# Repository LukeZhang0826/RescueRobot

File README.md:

# RescueRobot

An autonomous line-following rescue robot, built for a competition at the University of
Waterloo's IDEAS Clinic. It follows a track, finds a coloured target, picks it up with a
servo claw, carries it to a safe zone, drops it, then finds the line again and drives
back.

We called it Hamster, which is why the robot code lives in `Hamster/`.

**[Watch the run](https://youtu.be/ffi4BYylVoE)** ·
**[Final report](https://docs.google.com/document/d/1Vht0kWhE6cIuxJ4qUaxeXvZQmihU7ujaP2H0h0Pqgro/edit)**

Built by Josh Lobe, Koketso Gaborekwe, Luke Zhang, Winters Xia, and Griffin Wilson.

## The mission

`Hamster/robot_mission.py` is a flat state machine. A button press starts it, and every
stage either advances or drops into an error state.

```
idle -> search_line_follow -> approach_target -> pickup -> holding_object
     -> turn_around -> rescue_line_follow -> approach_safe_zone -> release
     -> find_line -> return_line_follow -> done
```

Three separate line followers exist because each leg of the run has different exit
conditions. `search_line_follower` stops when the target is large enough in frame,
`rescue_line_follower` stops on the safe zone signature, and `return_line_follow` runs
the trip home. All three share a PD steering loop over the Pixy2 line centroid, with a
recovery state that turns back toward the side the line was last seen on.

## Hardware

| Part | Notes |
| --- | --- |
| Raspberry Pi Pico | Runs the MicroPython mission code in `Hamster/` |
| Arduino Mega 2560 | PlatformIO firmware in `firmware/`, used for board bring-up |
| Pixy2 camera | Line tracking and colour connected component detection, 7 signatures |
| DRV8833 | Dual motor driver, signed speed from -100 to +100 |
| Servo claw | Pickup and release |
| Custom PCBs | An Arduino Mega shield and a base board, KiCad sources in `Electrical/` |

Both PCBs were manufactured through JLCPCB. Gerbers, BOM, and pick-and-place files are
committed under `Electrical/KiCad/BasePCB/jlcpcb/`.

## Layout

| Path | What it is |
| --- | --- |
| `Hamster/` | MicroPython mission code for the Pico |
| `Hamster/archive/` | Superseded scripts kept from earlier milestones |
| `Hamster/pixycamParams/` | Saved Pixy2 tuning, including the values used on the day |
| `firmware/` | PlatformIO project for the Arduino Mega |
| `Electrical/KiCad/` | KiCad projects, gerbers, and production files |

## Running it

The Pico code is deployed with the MicroPico VS Code extension. Copy the contents of
`Hamster/` to the board and reset it. `Hamster/main.py` wires up the hardware objects and
hands control to `RobotMission.run_once()`, which waits for the start button.

Everything the robot is tuned by lives in `Hamster/config.py`, including the PI gains per
wheel, the PD steering constants, base speeds in RPM, and the Pixy2 area thresholds that
decide when a target is close enough to stop. The competition values are the ones
currently committed.

For the Arduino side, `cd firmware && pio run -t upload`.

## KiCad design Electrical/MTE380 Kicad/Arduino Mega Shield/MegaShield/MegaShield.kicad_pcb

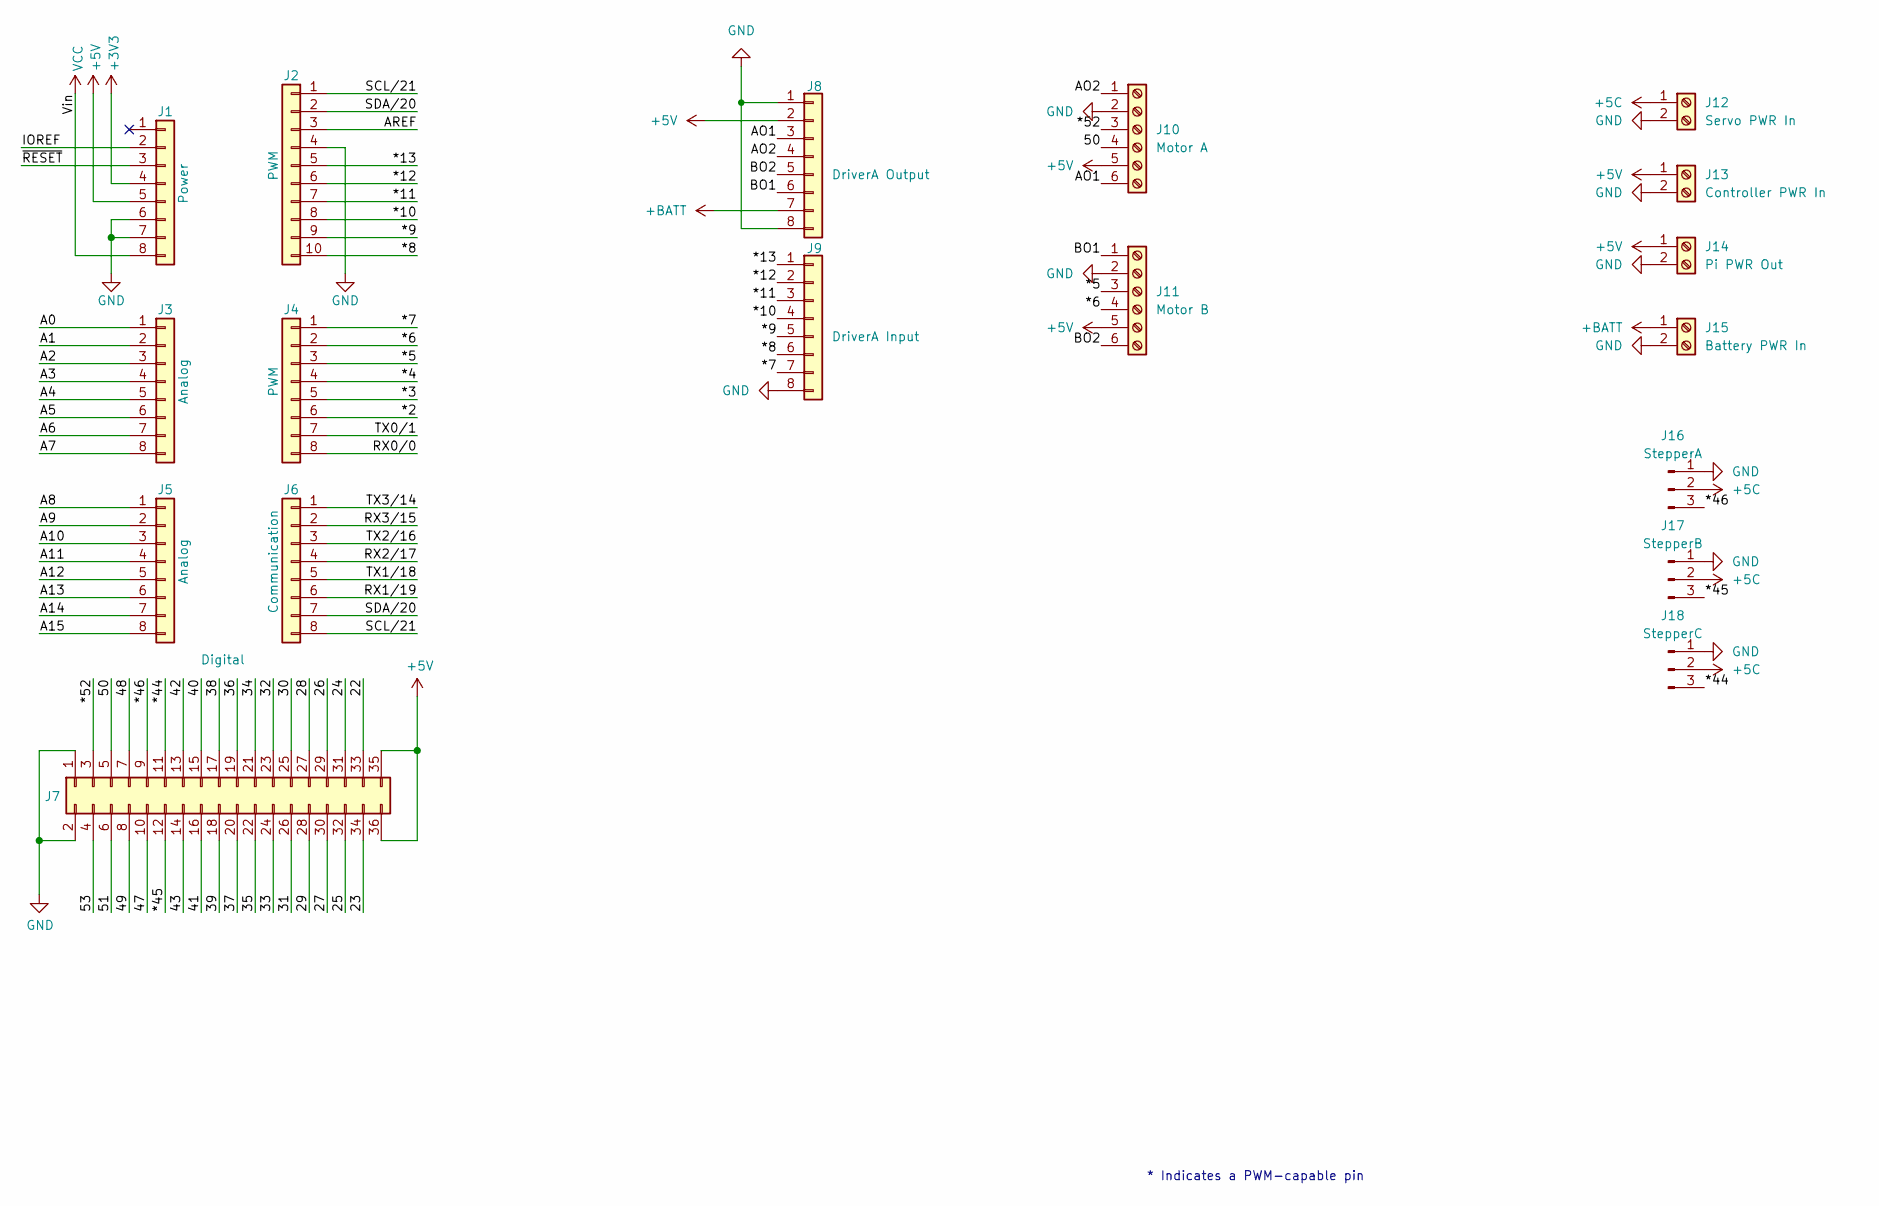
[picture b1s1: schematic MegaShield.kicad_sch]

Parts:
J1: Power; PinSocket_1x08_P2.54mm_Vertical
J2: PWM; PinSocket_1x10_P2.54mm_Vertical
J3, J5: Analog; PinSocket_1x08_P2.54mm_Vertical
J4: PWM; PinSocket_1x08_P2.54mm_Vertical
J6: Communication; PinSocket_1x08_P2.54mm_Vertical
J7: Digital; PinSocket_2x18_P2.54mm_Vertical
J8: DriverA Output; PinSocket_1x08_P2.54mm_Vertical
J9: DriverA Input; PinSocket_1x08_P2.54mm_Vertical
J10: Motor A; TerminalBlock_4Ucon_1x06_P3.50mm_Horizontal
J11: Motor B; TerminalBlock_4Ucon_1x06_P3.50mm_Horizontal
J12: Servo PWR In; TerminalBlock_CUI_TB007-508-02_1x02_P5.08mm_Horizontal
J13: Controller PWR In; TerminalBlock_CUI_TB007-508-02_1x02_P5.08mm_Horizontal
J14: Pi PWR Out; TerminalBlock_CUI_TB007-508-02_1x02_P5.08mm_Horizontal
J15: Battery PWR In; TerminalBlock_CUI_TB007-508-02_1x02_P5.08mm_Horizontal
J16: StepperA; PinSocket_1x03_P2.54mm_Vertical
J17: StepperB; PinSocket_1x03_P2.54mm_Vertical
J18: StepperC; PinSocket_1x03_P2.54mm_Vertical

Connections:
+3V3: J1.4
+5C: J12.1, J16.2, J17.2, J18.2
+5V: J1.5, J7.35, J7.36, J8.2, J10.5, J11.5, J13.1, J14.1
+BATT: J8.7, J15.1
/22: J7.33
/23: J7.34
/24: J7.31
/25: J7.32
/26: J7.29
/27: J7.30
/28: J7.27
/29: J7.28
/30: J7.25
/31: J7.26
/32: J7.23
/33: J7.24
/34: J7.21
/35: J7.22
/36: J7.19
/37: J7.20
/38: J7.17
/39: J7.18
/40: J7.15
/41: J7.16
/42: J7.13
/43: J7.14
/47: J7.10
/48: J7.7
/49: J7.8
/50: J7.5, J10.4
/51: J7.6
/53: J7.4
/*2: J4.6
/*3: J4.5
/*4: J4.4
/*5: J4.3, J11.3
/*6: J4.2, J11.4
/*7: J4.1, J9.7
/*8: J2.10, J9.6
/*9: J2.9, J9.5
/*10: J2.8, J9.4
/*11: J2.7, J9.3
/*12: J2.6, J9.2
/*13: J2.5, J9.1
/*44: J7.11, J18.3
/*45: J7.12, J17.3
/*46: J7.9, J16.3
/*52: J7.3, J10.3
/A0: J3.1
/A1: J3.2
/A2: J3.3
/A3: J3.4
/A4: J3.5
/A5: J3.6
/A6: J3.7
/A7: J3.8
/A8: J5.1
/A9: J5.2
/A10: J5.3
/A11: J5.4
/A12: J5.5
/A13: J5.6
/A14: J5.7
/A15: J5.8
/AO1: J8.3, J10.6
/AO2: J8.4, J10.1
/AREF: J2.3
/BO1: J8.6, J11.1
/BO2: J8.5, J11.6
/IOREF: J1.2
/RX0/0: J4.8
/RX1/19: J6.6
/RX2/17: J6.4
/RX3/15: J6.2
/SCL/21: J2.1, J6.8
/SDA/20: J2.2, J6.7
/TX0/1: J4.7
/TX1/18: J6.5
/TX2/16: J6.3
/TX3/14: J6.1
/~RESET: J1.3
GND: J1.6, J1.7, J2.4, J7.1, J7.2, J8.1, J8.8, J9.8, J10.2, J11.2, J12.2, J13.2, J14.2, J15.2, J16.1, J17.1, J18.1
VCC: J1.8

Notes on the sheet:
* Indicates a PWM-capable pin

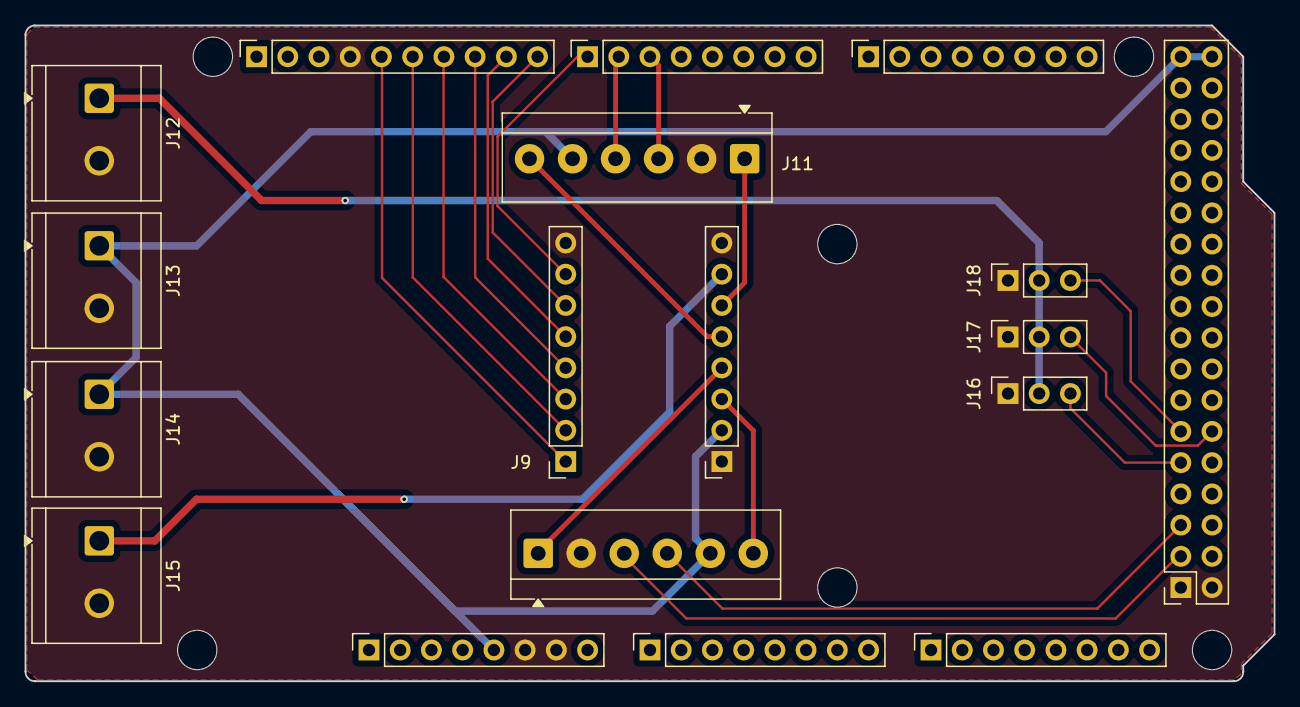
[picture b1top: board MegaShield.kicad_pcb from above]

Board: 2 copper layers, 101.6 x 53.3 mm, 24 parts (0 on the bottom side), 24 nets.

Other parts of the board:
MH1, MH2, MH3, MH4, MH5, MH6: MountingHole_3.2mm

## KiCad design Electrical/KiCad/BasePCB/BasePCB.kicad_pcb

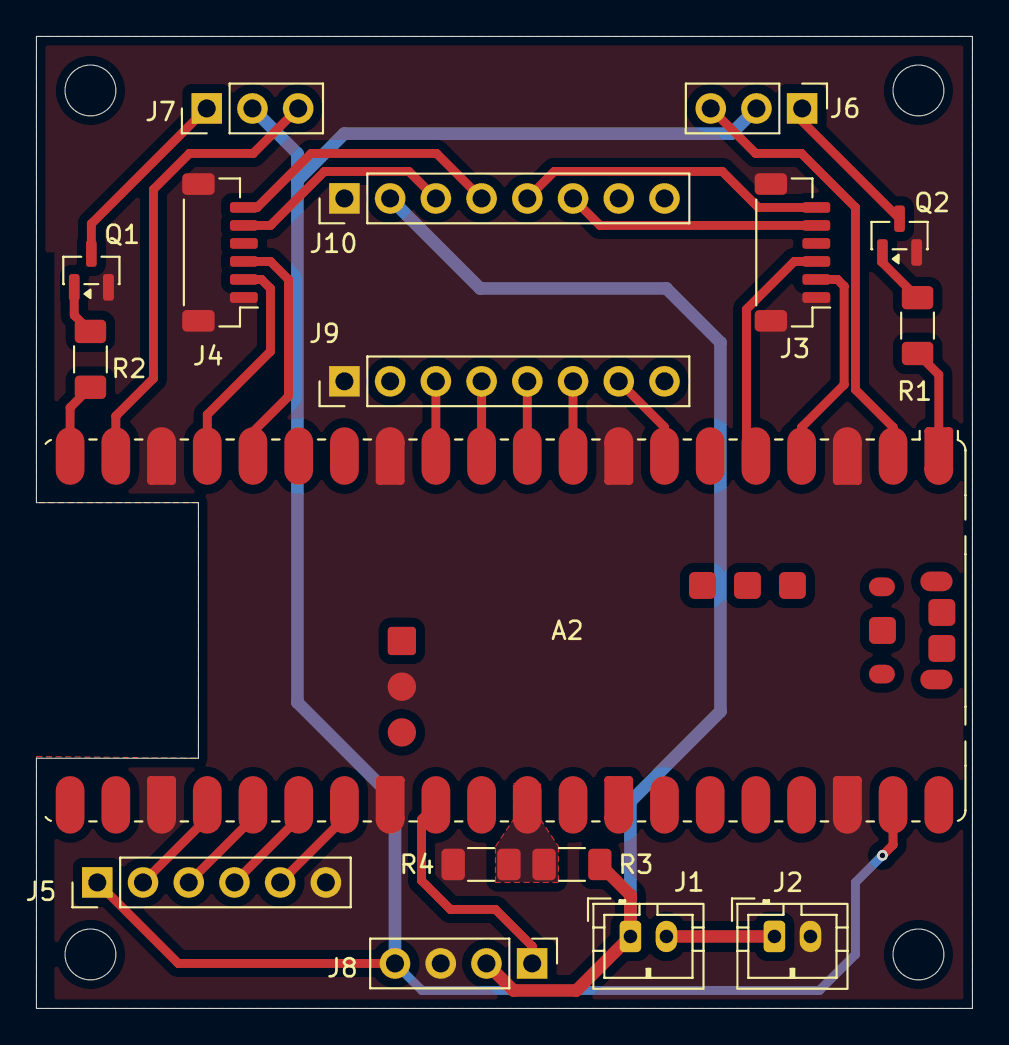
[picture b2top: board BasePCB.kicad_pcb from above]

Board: 2 copper layers, 52.0 x 54.0 mm, 17 parts (0 on the bottom side), 32 nets.

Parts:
A2: RaspberryPi_Pico_W; RaspberryPi_Pico_W_SMD
J1, J2: Conn_01x02_Socket; JST_PH_B2B-PH-K_1x02_P2.00mm_Vertical
J3, J4: Conn_01x06_Socket; JST_SH_BM06B-SRSS-TB_1x06-1MP_P1.00mm_Vertical
J5: Conn_01x06; PinHeader_1x06_P2.54mm_Vertical
J6, J7: Conn_01x03; PinHeader_1x03_P2.54mm_Vertical
J8: Conn_01x04; PinHeader_1x04_P2.54mm_Vertical
J9, J10: Conn_01x08; PinHeader_1x08_P2.54mm_Vertical
Q1, Q2: AO3400A; SOT-23
R1, R2: 10k; R_1206_3216Metric_Pad1.30x1.75mm_HandSolder
R3: 100k; R_1206_3216Metric_Pad1.30x1.75mm_HandSolder
R4: 56k; R_1206_3216Metric_Pad1.30x1.75mm_HandSolder

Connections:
+3.3V: A2.36 (3V3), J3.4, J4.4
+5V: A2.39 (VSYS), J5.1, J6.2, J7.2, J8.4
+BATT: J1.1, J8.2, J10.2, R3.1
/5V_EN: A2.29 (GPIO22), J8.1
/AIN1: A2.9 (GPIO6), J9.6
/AIN2: A2.10 (GPIO7), J9.5
/BIN1: A2.12 (GPIO9), J9.3
/BIN2: A2.11 (GPIO8), J9.4
/CLK: A2.24 (GPIO18), J5.2
/CS: A2.27 (GPIO21), J5.5
/EA1: A2.4 (GPIO2), J3.2
/EA2: A2.5 (GPIO3), J3.3
/EB1: A2.17 (GPIO13), J4.2
/EB2: A2.16 (GPIO12), J4.3
/MA1: J3.5, J10.6
/MA2: J3.6, J10.5
/MB1: J4.5, J10.3
/MB2: J4.6, J10.4
/MISO: A2.26 (GPIO20), J5.4
/MOSI: A2.25 (GPIO19), J5.3
/SA_PWM: A2.2 (GPIO1), J6.3
/SA_PWR: A2.1 (GPIO0), R1.1
/SB_PWM: A2.19 (GPIO14), J7.3
/SB_PWR: A2.20 (GPIO15), R2.1
/Vchg: A2.31 (GPIO26_ADC0), R3.2, R4.1
/nSLEEP: A2.7 (GPIO5), J9.7
GND: A2.3 (GND), A2.8 (GND), A2.13 (GND), A2.18 (GND), A2.23 (GND), A2.28 (GND), A2.38 (GND), A2.D2 (GND), J2.2, J3.1, J3.MP, J4.1, J4.MP, J5.6, J8.3, J9.1, J10.1, Q1.2 (S), Q2.2 (S), R4.2
unnamed: J1.2, J2.1
unnamed: J6.1, Q2.3 (D)
unnamed: J7.1, Q1.3 (D)
unnamed: Q1.1 (G), R2.2
unnamed: Q2.1 (G), R1.2

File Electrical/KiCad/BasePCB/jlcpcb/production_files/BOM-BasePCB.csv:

Comment,Designator,Footprint,LCSC,Quantity
Conn_01x06_Socket,J3,JST_SH_BM06B-SRSS-TB_1x06-1MP_P1.00mm_Vertical,,1
RaspberryPi_Pico_W,A2,RaspberryPi_Pico_W_SMD,,1
10k,R2,R_1206_3216Metric_Pad1.30x1.75mm_HandSolder,,1
Conn_01x06_Socket,J4,JST_SH_BM06B-SRSS-TB_1x06-1MP_P1.00mm_Vertical,,1
10k,R1,R_1206_3216Metric_Pad1.30x1.75mm_HandSolder,,1
AO3400A,Q2,SOT-23,,1
Conn_01x03,J7,PinHeader_1x03_P2.54mm_Vertical,,1
Conn_01x03,J6,PinHeader_1x03_P2.54mm_Vertical,,1
Conn_01x02_Socket,J1,JST_PH_B2B-PH-K_1x02_P2.00mm_Vertical,,1
Conn_01x02_Socket,J2,JST_PH_B2B-PH-K_1x02_P2.00mm_Vertical,,1
Conn_01x08,J10,PinHeader_1x08_P2.54mm_Vertical,,1
Conn_01x08,J9,PinHeader_1x08_P2.54mm_Vertical,,1
56k,R4,R_1206_3216Metric_Pad1.30x1.75mm_HandSolder,,1
100k,R3,R_1206_3216Metric_Pad1.30x1.75mm_HandSolder,,1
Conn_01x04,J8,PinHeader_1x04_P2.54mm_Vertical,,1
AO3400A,Q1,SOT-23,,1
Conn_01x06,J5,PinHeader_1x06_P2.54mm_Vertical,,1

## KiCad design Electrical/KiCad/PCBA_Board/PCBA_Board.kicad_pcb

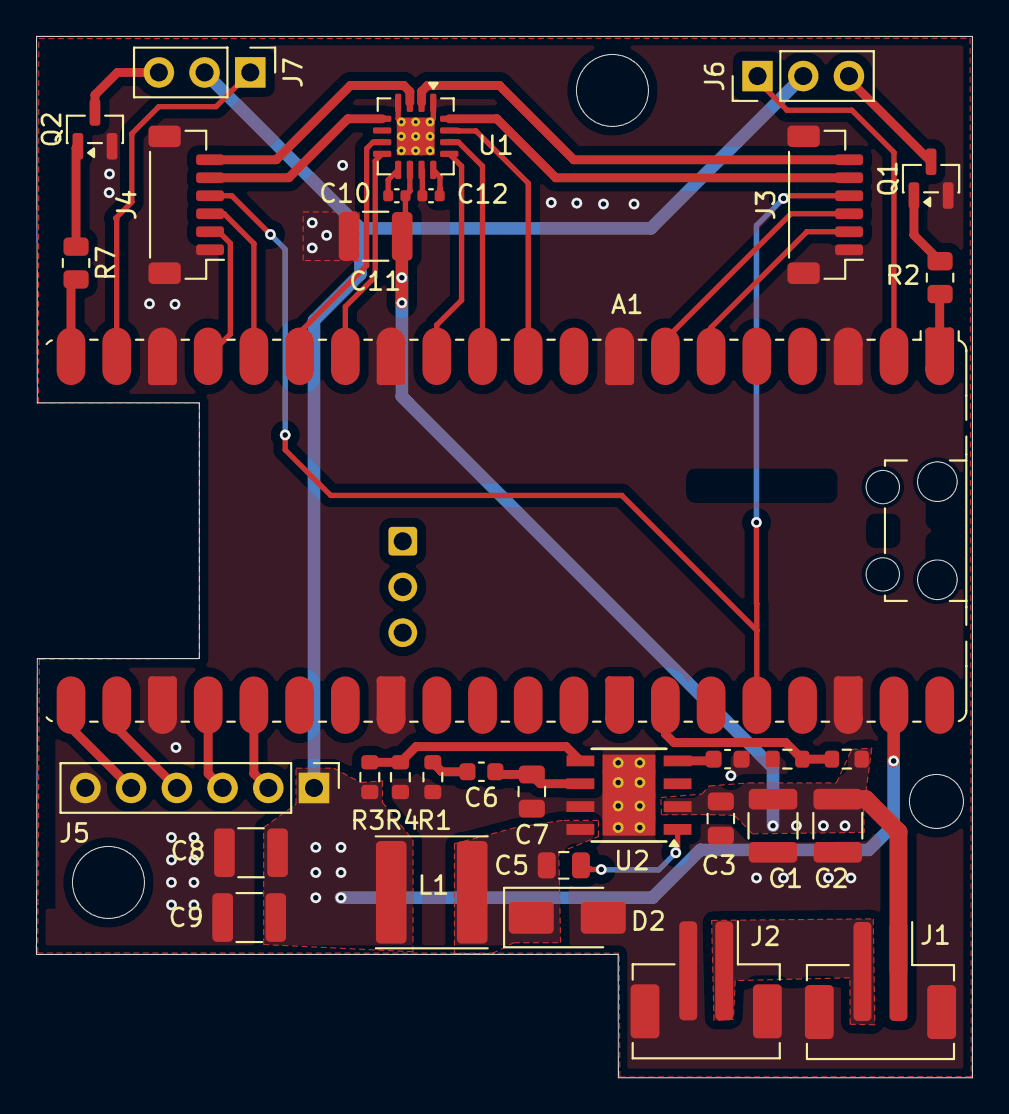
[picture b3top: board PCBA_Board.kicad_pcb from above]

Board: 2 copper layers, 52.0 x 57.8 mm, 33 parts (0 on the bottom side), 39 nets.

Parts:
A1: RaspberryPi_Pico_W; RaspberryPi_Pico_W_SMD_HandSolder
C1, C2: 4.7uF; C_1210_3225Metric
C3: 0.01uF; C_0805_2012Metric
C4: 8.2nF; C_0603_1608Metric
C5: 100nF; C_0805_2012Metric
C6: 1nF; C_0603_1608Metric
C7: 10pF; C_0805_2012Metric
C8, C9: 47u; C_1210_3225Metric
C10: 0.01u; C_0402_1005Metric
C11: 10u; C_1210_3225Metric
C12: 2.2u; C_0402_1005Metric
D2: SS24; D_SMA
J1: Batt_1; JST_PH_B2B-PH-SM4-TB_1x02-1MP_P2.00mm_Vertical
J2: Batt_2; JST_PH_B2B-PH-SM4-TB_1x02-1MP_P2.00mm_Vertical
J3: MotorA; JST_SH_BM06B-SRSS-TB_1x06-1MP_P1.00mm_Vertical
J4: MotorB; JST_SH_BM06B-SRSS-TB_1x06-1MP_P1.00mm_Vertical
J5: Pixy SPI Connection; PinHeader_1x06_P2.54mm_Vertical
J6: ServoA; PinHeader_1x03_P2.54mm_Vertical
J7: ServoB; PinHeader_1x03_P2.54mm_Vertical
L1: 4.7u; L_APV_ANR6028
Q1, Q2: AO3400A; SOT-23
R1: 66.5k; R_0603_1608Metric
R2, R7: 100k; R_0805_2012Metric
R3: 10.2k; R_0603_1608Metric
R4: 1.96k; R_0603_1608Metric
R5: 570K; R_0603_1608Metric
R6: 330K; R_0603_1608Metric
U1: DRV8833RTY; Texas_RTY_WQFN-16-1EP_4x4mm_P0.65mm_EP2.1x2.1mm_ThermalVias
U2: TPS54331; TI_SO-PowerPAD-8_ThermalVias

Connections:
+3.3V: A1.36 (3V3), J3.4, J4.4
+5V: A1.39 (VSYS), C8.1, C9.1, J5.1, J6.2, J7.2, L1.2, R3.1
+BATT: C1.1, C2.1, C3.1, C10.1, C11.1, J1.1, R5.1, U1.10 (VM), U2.2 (Vin)
/AIN1: A1.11 (GPIO8), U1.14 (AIN1)
/AIN2: A1.12 (GPIO9), U1.13 (AIN2)
/AOUT1: J3.5, U1.16 (AOUT1)
/AOUT2: J3.6, U1.2 (AOUT2)
/BIN1: A1.15 (GPIO11), U1.7 (BIN1)
/BIN2: A1.14 (GPIO10), U1.8 (BIN2)
/BOUT1: J4.5, U1.5 (BOUT1)
/BOUT2: J4.6, U1.3 (BOUT2)
/CS: A1.22 (GPIO17), J5.4
/ENC_A1: A1.6 (GPIO4), J3.2
/ENC_A2: A1.7 (GPIO5), J3.3
/ENC_B1: A1.17 (GPIO13), J4.2
/ENC_B2: A1.16 (GPIO12), J4.3
/MISO: A1.21 (GPIO16), J5.5
/MOSI: A1.25 (GPIO19), J5.2
/SCK: A1.24 (GPIO18), J5.3
/ServoA_PWM: A1.2 (GPIO1), J6.1
/ServoA_PWR: A1.1 (GPIO0), R2.2
/ServoB_PWM: A1.19 (GPIO14), J7.1
/ServoB_PWR: A1.20 (GPIO15), R7.2
/VbatSense: A1.34 (GPIO28_ADC2), R5.2, R6.1
/Vsns: R3.2, R4.1, U2.5 (Vsense)
/nSleep: A1.10 (GPIO7), U1.15 (~SLEEP)
GND: A1.3 (GND), A1.8 (GND), A1.13 (GND), A1.18 (GND), A1.23 (GND), A1.28 (GND), A1.38 (GND), C1.2, C2.2, C3.2, C4.2, C7.2, C8.2, C9.2, C11.2, C12.1, D2.2 (A), J1.MP (MountPin), J2.2, J2.MP (MountPin), J3.1, J3.MP (MountPin), J4.1, J4.MP (MountPin), J5.6, Q1.2 (S), Q2.2 (S), R1.2, R4.2, R6.2, U1.1 (AISEN), U1.4 (BISEN), U1.11 (GND), U1.17 (GND), U2.7 (GND), U2.9 (EP)
unnamed: C6.2, R1.1
unnamed: C5.1, D2.1 (K), L1.1, U2.8 (PH)
unnamed: J1.2, J2.1
unnamed: J6.3, Q1.3 (D)
unnamed: J7.3, Q2.3 (D)
unnamed: Q1.1 (G), R2.1
unnamed: Q2.1 (G), R7.1
unnamed: C10.2, U1.9 (VCP)
unnamed: C12.2, U1.12 (VINT)
unnamed: C5.2, U2.1 (BOOT)
unnamed: C6.1, C7.1, U2.6 (COMP)
unnamed: C4.1, U2.4 (SS)

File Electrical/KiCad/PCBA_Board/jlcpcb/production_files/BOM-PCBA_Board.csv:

Comment,Designator,Footprint,LCSC,Quantity
0.01u,C10,C_0402_1005Metric,C1524,1
0.01uF,C3,C_0805_2012Metric,C123143,1
1.96k,R4,R_0603_1608Metric,C22854,1
10.2k,R3,R_0603_1608Metric,C22772,1
100k,"R2,R7",R_0805_2012Metric,C25611,2
100nF,C5,C_0805_2012Metric,C1711,1
10pF,C7,C_0805_2012Metric,C107107,1
10u,C11,C_1210_3225Metric,C39232,1
1nF,C6,C_0603_1608Metric,C1587,1
2.2u,C12,C_0402_1005Metric,C72203,1
330K,R6,R_0603_1608Metric,C23137,1
4.7u,L1,L_APV_ANR6028,C78804,1
4.7uF,"C1,C2",C_1210_3225Metric,C47783,2
47u,"C8,C9",C_1210_3225Metric,C77101,2
570K,R5,R_0603_1608Metric,C23178,1
66.5k,R1,R_0603_1608Metric,C23225,1
8.2nF,C4,C_0603_1608Metric,C113812,1
AO3400A,"Q1,Q2",SOT-23,C20917,2
Batt_1,J1,JST_PH_B2B-PH-SM4-TB_1x02-1MP_P2.00mm_Vertical,C265003,1
Batt_2,J2,JST_PH_B2B-PH-SM4-TB_1x02-1MP_P2.00mm_Vertical,C265003,1
DRV8833RTY,U1,Texas_RTY_WQFN-16-1EP_4x4mm_P0.65mm_EP2.1x2.1mm_ThermalVias,C154936,1
MotorA,J3,JST_SH_BM06B-SRSS-TB_1x06-1MP_P1.00mm_Vertical,C160392,1
MotorB,J4,JST_SH_BM06B-SRSS-TB_1x06-1MP_P1.00mm_Vertical,C160392,1
Pixy SPI Connection,J5,PinHeader_1x06_P2.54mm_Vertical,C37208,1
RaspberryPi_Pico_W,A1,RaspberryPi_Pico_W_SMD_HandSolder,C42394205,1
SS24,D2,D_SMA,C50645,1
ServoA,J6,PinHeader_1x03_P2.54mm_Vertical,C49257,1
ServoB,J7,PinHeader_1x03_P2.54mm_Vertical,C49257,1
TPS54331,U2,TI_SO-PowerPAD-8_ThermalVias,C90761,1

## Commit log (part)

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2026-01-30 rayan's code
2026-01-30 platformio
2026-01-30 Scaffold the PlatformIO project for the Arduino Mega
2026-01-30 pins header file
2026-01-30 Move pin assignments into pins.h
2026-01-30 interfacing pi and arduino
2026-01-30 Wire the Pi to the Arduino over serial
2026-01-30 Add the Arduino Mega shield KiCad project and gerbers
2026-01-30 Added PCB Files
2026-01-30 added pin header file
2026-01-30 Add config.h with the shared hardware configuration
2026-01-30 removed pins.h
2026-01-30 Drop pins.h now that config.h holds the assignments
2026-02-04 Finish the base PCB with a socketed buck and motor controller
2026-02-04 Finished PCB with socketed buck and motor controller
2026-02-05 added all the pcb shit
2026-02-05 Add the base PCB gerbers and JLCPCB production files
2026-02-27 add motor control script for PWM speed management
2026-02-27 Add a motor control script for PWM speed management
2026-02-27 Add test firmware for the motor board
2026-02-27 added testing firmware
2026-02-28 Move the robot code into the Hamster package
2026-02-28 hamster
2026-02-28 initial ccc detection
2026-02-28 Add initial Pixy2 color connected component detection
2026-03-04 pid time
2026-03-04 Add PID speed control for the drive motors
2026-03-05 milestone4
2026-03-05 Add servo control and a camera follow routine
2026-03-05 idk i think it kind of works
2026-03-05 Try a first pass at the main mission loop
2026-03-05 Revert "idk i think it kind of works"
    This reverts commit f05334250fec54de9ecd49d1204abe5ed732881c.
2026-03-05 Revert the first pass at the main mission loop
2026-03-05 straight line test
2026-03-05 Add a straight line drive test and archive earlier scripts
2026-03-05 basic_movements
2026-03-05 Add basic movement primitives and a start button
2026-03-06 Refactor servo angles, add Pixy2 camera and line follower classes, and remove obsolete speed test file
2026-03-06 Refactor servo angles and add Pixy2 camera and line follower classes
2026-03-06 Add a basic movement test entry point
2026-03-06 basic movements test
2026-03-06 demo1
2026-03-06 Wire line following into the main loop for the first demo
2026-03-18 line following fucking works in this commit
2026-03-18 Get line following working reliably
2026-03-19 Detect all seven Pixy2 color signatures
2026-03-19 all color signatures work
2026-03-19 approach target
2026-03-19 Add target approach and archive the old motor controller
2026-03-19 breaking kind of works
2026-03-19 Add braking to the line follower
2026-03-19 state machine
2026-03-19 Add the mission state machine
2026-03-20 Update robot_mission.py - stop after search line follow
2026-03-20 Stop after the search line follow stage
2026-03-20 top middle centroid detection
2026-03-20 Use the top middle centroid for target detection
2026-03-20 Update state machine: link approach target to pickup, update config
2026-03-20 Link target approach into pickup in the state machine
2026-03-20 Finish the state machine and add the claw controller
2026-03-20 finished state machine
2026-03-23 Split the rescue and return line followers
2026-03-23 performance optimization
2026-03-23 Drop base speed to 150 rpm and retune the steering gains
2026-03-23 last working 150 rpm
2026-03-23 Add the remaining electrical files
2026-03-24 Rework the claw controller, line following regressed
2026-03-24 better values for game day
2026-03-24 Retune the line follower and servo values for the competition run
2026-03-24 push gamedayvalues
2026-03-24 Add the Pixy2 parameter dump used on competition day
2026-03-24 Shorten the safe zone and find line drive counts
2026-03-24 more better values
2026-03-26 Retune the steering limits and raise the stop target area
2026-03-26 better values
2026-03-26 Add a line recovery state to the followers
2026-03-26 intro to recovery state
2026-03-26 increase speed and stuff
2026-03-26 Raise base speed to 250 rpm and narrow the turn differential
2026-03-26 Rename the rescue follower to search follower and hoist elapsed time
2026-03-26 Restore the rescue follower name and read the safe zone off signature 7
2026-03-26 Extend line recovery across the return follower
2026-03-26 Set the final competition values, 200 rpm and 1500 stop area
